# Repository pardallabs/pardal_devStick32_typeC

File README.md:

# pardal_devStick32_typeC
Pardallabs Development Stick ESP32 Type C

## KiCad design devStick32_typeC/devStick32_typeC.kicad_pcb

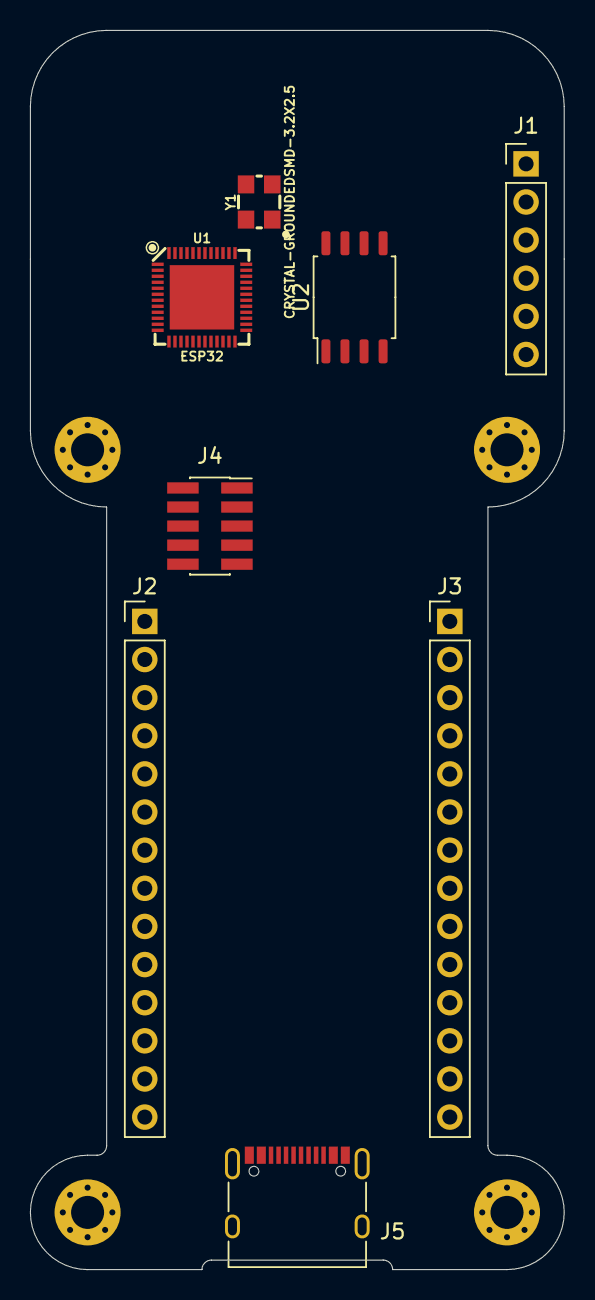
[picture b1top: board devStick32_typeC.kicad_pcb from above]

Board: 2 copper layers, 35.6 x 82.6 mm, 8 parts (0 on the bottom side), 5 nets, no tracks yet.

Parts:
J1: Conn_01x06_Male; PinHeader_1x06_P2.54mm_Vertical
J2, J3: Conn_01x14_Male; PinHeader_1x14_P2.54mm_Vertical
J4: Conn_02x05_Odd_Even; PinSocket_2x05_P1.27mm_Vertical_SMD
J5: CX70M-24P1; USB_C_Receptacle_XKB_U262-16XN-4BVC11
U1: ESP32; QFN48-0.4MM
U2: W25Q32JVSS; SOIC-8_5.23x5.23mm_P1.27mm
Y1: CRYSTAL-GROUNDEDSMD-3.2X2.5; CRYSTAL-SMD-3.2X2.5MM

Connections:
+3V3: J2.1, J3.1
GND: J2.2, J2.14, J3.2, J3.14
unnamed: U1.1, U1.43, U1.46
unnamed: U1.3, U1.4
unnamed: Y1.2, Y1.4

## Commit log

2020-03-15 Initial version and files added to the project
2020-03-15 Defined the outlayer and basic connectors as default format for the DStick
2020-03-15 Added ESP32-D0 on schema and PCB
2020-03-29 Added memory, xtal and labels
